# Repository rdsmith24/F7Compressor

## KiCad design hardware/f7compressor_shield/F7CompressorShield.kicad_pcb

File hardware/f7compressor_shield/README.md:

# F7Compressor carrier PCB (NUCLEO shield)

KiCad 10 project for a board that the NUCLEO-H723ZG plugs into directly,
replacing the point-to-point jumper wiring in `../../wiring_diagram.html`
between the NUCLEO and the LCD module, relay module, oil-pressure switch,
e-stop, and 4-20mA pressure loop. Open `F7CompressorShield.kicad_pro`.

## What's actually in this first pass

- **Schematic (`.kicad_sch`)**: complete and ERC-clean (0 errors, 0 warnings).
  Every net is named after the signal names used elsewhere in this repo
  (`FMC_D0`, `TP_SCK`, `RELAY_RUN`, `OIL_SW`, `ESTOP`, `PRESSURE_SENSE`,
  etc.) and was transcribed pin-by-pin from the FMC/SPI5/Analog&Digital I/O
  tables in `wiring_diagram.html`. Pins that are intentionally not used are
  marked with no-connect flags rather than left silently floating, so the
  schematic documents "unused" vs. "forgot to wire" explicitly.
- **PCB (`.kicad_pcb`)**: all 23 footprints (14 components + 4 LCD mounting
  holes + 5 Nucleo mounting holes) placed with correct net assignments, on
  **one unified board outline** (191.23 x 182.65mm). **Fully routed**: all
  39 nets, 2 layers, 537 track segments, 23 vias, 0 unconnected items —
  see "Routing" below for how.
- Two footprint groups on that one outline:
  - **NUCLEO-mating cluster** (`U1`, `CN7`-`CN10`), top-left: laid out to
    mirror where these connectors actually sit under the real NUCLEO-144
    board, with a **true-to-size reference outline** (70 x 133.34mm —
    the full board *with* the ST-Link section, since that's staying
    attached; `Dwgs.User` layer) drawn around it and 5 mounting holes
    (4 corners + 1 off-center, matching UM1974 Figure 7) — see "Mechanical
    layout" and "Nucleo mounting holes" below.
  - **Field-wiring group** (`J1`, `J2`, `SW1`-`SW3`, `J5`, `J6`, `R1`, `C1`, plus
    4 unreferenced LCD mounting-hole footprints): the LCD header (`J1`)
    top-right — positioned and surrounded by 4 mounting holes that
    reproduce the real LCD module's hole pattern, see "LCD mounting" below
    — with the relay header, simulation toggle switches, and pressure-loop
    terminal stacked below it, i.e. to the right of the Nucleo cluster and
    down from the LCD, per request. Each part is left-aligned and stacked
    using its own real footprint bounding box (`stack_right()` in
    `gen_pcb.py`), so the gaps stay correct no matter how large or
    asymmetric an individual footprint's silkscreen/pads are (the terminal
    block and the resistor, in particular, both extend well to one side of
    their placement origin).
- Reference designators: `CN7`–`CN10` are the NUCLEO Zio headers (female
  sockets, mate directly with the NUCLEO board), `U1` is the Morpho
  connector pair (CN11+CN12, see below), `J1` is the LCD module header,
  `J2` is the relay module's control header, `SW1`-`SW3` are the on-board
  MTS-1 toggle switches (oil switch / e-stop / motor run sense), `J5` is
  the pressure-loop field terminal, `J6` is the 5VDC power input terminal
  (see "Power input" below), `R1`/`C1` are the pressure loop's 150Ω shunt
  and 100nF decoupling cap.

## Oil switch / e-stop / run-sense: on-board MTS-1 switches, not field terminals

`OIL_SW` and `ESTOP` used to be 2-pin screw terminals for wiring in the
real field switches. They're now **on-board MTS-1 SPDT toggle switches**
(`SW1`, `SW2`) instead, so the oil-pressure-fault and e-stop conditions can
be flipped directly on the bench without needing the actual field hardware
wired up — useful for firmware bring-up. `SW3` adds a third switch for a
**`RUN_SENSE`** net simulating motor-running feedback (see below).

- Each switch is used as a simple SPST: the common pole (pin 2, physically
  the MTS-1's center pin) goes to the signal net (`OIL_SW` / `ESTOP` /
  `RUN_SENSE`), one throw (pin 1) goes to `GND`, and the third throw (pin 3)
  is left unconnected. Toggling the switch mimics a NC switch's two states —
  closed (pin2–pin1 connected, net pulled to GND) or open (net floating,
  pulled HIGH by the MCU's internal pull-up).
- **Real part: Dailywell `1MS1T1B1M1QES-5`** (SPDT, PC-pin, same MTS-1
  family). No bundled KiCad footprint matches it, so `gen_pcb.py`'s
  `make_mts1_footprint()` builds it directly: 3 round THT pads, center pad
  (pin 2, common) drawn square to mark pin 1. Pin spacing confirmed against
  the real part's own listed dimensions at **4.70mm** — matches this
  footprint exactly, no change needed.
- **No PCB mounting hole for the bushing**: the real part has a confirmed
  6.35mm (0.25") mounting bushing, but that's nearly as wide as its whole
  body (6.86mm) — there's no room for it to sit beside the 3 pins within
  that footprint. That's strong physical evidence this bushing mounts
  through an enclosure panel cutout, not the PCB (the electrical pins
  solder to the board; the switch's mechanical mounting is panel-side).
  Confirmed with the user before leaving it out rather than guessing a
  PCB-side hole position that doesn't physically make sense.
- `J3`/`J4` (the old terminal references) no longer exist; `J5` (pressure
  loop) is unchanged since it isn't a switch — the 4-20mA loop still needs
  a real field terminal, not a toggle.

### Generic 3D model for `SW1`-`SW3`

No bundled or downloadable 3D model matches this part (or any close
MTS-1-family equivalent), so a simple placeholder was built by hand —
`3dmodels/SW_MTS1_generic.wrl`, a black box (body) plus a cylinder+sphere
(lever stub), sized to the real part's known 12.7 x 6.86mm body envelope.
It's explicitly a generic stand-in for visualization ("can be any brand"),
not a dimensionally accurate model of the real switch.

Attaching it surfaced a real scaling bug, found by measurement rather than
guessing: KiCad interprets raw VRML coordinates at a fixed 2.54 scale
(mm per 0.1", a legacy VRML convention) regardless of what unit the model
was actually authored in. The model here is authored directly in mm, so
`m_Scale = 1/2.54` is needed to display it correctly. The first attempt
assumed the usual inches-to-mm factor (`1/25.4`) and undershot by 10x
(rendered as a barely-visible speck); the actual factor was found by
pixel-measuring the rendered box at `scale=1.0` against the footprint's
own known pad pitch (a precise, calibrated measurement, not an estimate)
and solving for the scale that makes the box match the real 12.7 x 6.86mm
footprint outline exactly — confirmed by rendering again afterward and
re-measuring. Model path is `${KIPRJMOD}/3dmodels/SW_MTS1_generic.wrl`,
project-relative so it travels with the repo.

### `RUN_SENSE` (`SW3`) — new signal, not in firmware yet

There is **no existing motor-running-feedback input anywhere in this
project** — `CLAUDE.md`'s state machine only ever commands the relay
(`RELAY_RUN`), it never reads back whether the motor actually started. This
switch wires up a net for that *future* feature, the same way the spare
relay channels (`RELAY_IN2`-`4`) were wired for future use:

| Net | MCU pin | NUCLEO connector | Configured anywhere today? |
|---|---|---|---|
| `RUN_SENSE` | `PC3` | CN9 pin 5 (Zio) | No — not in CubeMX, not in `CLAUDE.md`, not read by any firmware |

`PC3` was picked because, like `PD6`/`PB1` for the spare relay channels,
it's unclaimed by any peripheral in `CLAUDE.md`'s pin tables. Using it for
real motor-run sensing later would need: CubeMX GPIO-input config for
`PC3`, a firmware read of it (e.g. in `compressor_sm.c`'s `RUNNING` state
to detect a stall/failed-start condition), and deciding what the state
machine should actually *do* with that information — none of which this
PCB-only change touches.

## Relay header (J2) — all 4 channels wired

The relay module is a 4-channel board but the firmware only drives channel
1 (`RELAY_RUN` = `PG4`, CN12 pin 69). The other 3 channels are now wired on
this board too, for future use, even though nothing drives them yet:

| J2 pin | Net | MCU pin | NUCLEO connector | Driven by firmware today? |
|---|---|---|---|---|
| 3 (IN1) | `RELAY_RUN` | `PG4` | CN12 pin 69 (Morpho) | Yes — `relay.c` |
| 4 (IN2) | `RELAY_IN2` | `PG5` | CN12 pin 68 (Morpho) | No — CubeMX already configures it as a GPIO output (`CLAUDE.md`), just unused |
| 5 (IN3) | `RELAY_IN3` | `PD6` | CN9 pin 4 (Zio) | No — not configured by CubeMX at all yet |
| 6 (IN4) | `RELAY_IN4` | `PB1` | CN9 pin 7 (Zio) | No — not configured by CubeMX at all yet |

`PG5`/`PD6`/`PB1` were picked because they're genuinely unclaimed by any
other peripheral in `CLAUDE.md`'s pin tables. Before IN2–IN4 can actually
be used, `PD6` and `PB1` need to be configured as GPIO outputs in CubeMX
(`PG5` already is) and the firmware needs a `Relay_Request()`-style call
added for each channel — this board only adds the physical wiring, it
doesn't change firmware.

## Power input (J6)

`J6` is a 2-pin screw terminal for an external 5VDC supply, so one
connector on this board can power the Nucleo and everything downstream of
it. **Real part: Phoenix Contact `1727010`** (MKDS 1/2-3,81 — confirmed
2-position, 3.81mm pitch, horizontal THT from distributor listings). KiCad
ships this exact footprint
(`TerminalBlock_Phoenix_MKDS-1-2-3.81_1x02_P3.81mm_Horizontal`), used
directly — no custom part needed, unlike the switches above. This
replaced the earlier generic placeholder (`TerminalBlock_MaiXu_MX126`,
5.08mm pitch). `J5` (pressure loop) uses the same real part and footprint
now too, once a part number was given for it.

- `J6` pin 1 (`+5V_IN`) goes to `U1` pin 6 — **Morpho CN11 pin 6, E5V** —
  the documented primary power source for this whole project
  (`wiring_diagram.html`'s Power table: "External 5 VDC adapter | CN11
  pin 6 (E5V) | Primary power source"). `J6` pin 2 goes to `GND`.
- **This is deliberately a separate net from the existing `+5V`** used for
  the relay module's VCC (sourced from Zio `CN8` pin 9). `CN8` pin 9 is
  the *Nucleo's own* regulated pass-through output, derived from E5V
  through the Nucleo's on-board power-source mux/protection circuitry —
  tying `+5V_IN` directly to it on our board would bypass that circuitry
  instead of feeding it properly. Once E5V is powered, `CN8` pin 9 should
  carry the same rail anyway (via the Nucleo's own hardware), so the
  relay's `+5V` wiring doesn't need to change.
- **A jumper move on the physical Nucleo board is required for this to
  actually work**: `JP2` has to be set to the `EXT` position (pins 5-6),
  per `CLAUDE.md`'s hardware summary — this is a jumper on the Nucleo
  itself, not something this shield can set for you.
- A `PWR_FLAG` symbol is attached to `+5V_IN` in the schematic — not a
  real component, just a standard KiCad marker asserting "this net is
  externally driven," needed because `E5V` is a `Power input`-typed pin
  that ERC otherwise expects a driving `Power output` pin for.

## What's routed vs. just present

Only the nets actually used by this design are wired — everything else on
the Zio/Morpho headers is populated (for mechanical fit) but left on
no-connect. See `CLAUDE.md` for the full signal-to-pin reference this was
built from.

## Morpho: CN11 and CN12 are real, separate connectors (not a combined part)

Three FMC data lines (`PD8`/`PD9`/`PD10` = `FMC_D13`-`D15`) and the RUN
relay (`PG4`) are only reachable on the Morpho connectors (CN11/CN12),
which are unpopulated from the factory — you solder male pin headers onto
the Nucleo at those two locations, and this shield needs matching female
sockets.

**This went through two iterations.** The first used KiCad's bundled
`Module:ST_Morpho_Connector_144_STLink` footprint (via the official
`MCU_Module:NUCLEO144-F429ZI` symbol) as a single combined part for both
CN11 and CN12, with pad numbers cross-checked against `CLAUDE.md`'s known
signals (pad N = CN11 pin N for N 1-72, pad N = CN12 pin N-72 for N
73-144 — `PD9`→pad 69→CN11 pin 69, `PG4`→pad 141→CN12 pin 69, `PD8`→pad
82→CN12 pin 10, `PD10`→pad 137→CN12 pin 65, all four verified). That
worked electrically, but direct inspection (prompted by counting pins on
the real board) found two real problems with it:

- The real `CN11`/`CN12` are each **35×2 (70-pin)** headers, confirmed
  from the NUCLEO-H723ZG schematic (sheet 5, "MORPHO CONNECTOR LEFT/RIGHT
  SIDE", labeled "Header 35x2"). `CLAUDE.md` previously said 2×38, which
  was wrong and has been corrected. The bundled footprint has 74 pads per
  side (148 total) — 8 more than the real connectors.
- It's **one footprint representing two physically separate connectors**,
  which doesn't match the real board and isn't something you can order as
  a single part.

**Current design**: `CN11` and `CN12` are two separate instances of the
same plain `Connector_Generic:Conn_02x35_Odd_Even` / `PinSocket_2x35_
P2.54mm_Vertical` part already used (and pin-1-verified) for `CN7`-`CN10`
— exactly 70 pads each, nothing extra. Pin numbers and GPIO assignments
are ST's own real-board numbering, from UM1974 Table 21 ("ST morpho
connector for NUCLEO-F207ZG, ..., NUCLEO-H743ZI" — the same family this
H723ZG board belongs to) — cross-checked against `CLAUDE.md` and found to
match exactly for all six signals actually used (`FMC_D13`→CN12 pin 10,
`FMC_D14`→CN11 pin 69, `FMC_D15`→CN12 pin 65, `RELAY_RUN`→CN12 pin 69,
`RELAY_IN2`→CN12 pin 68, `+5V_IN`→CN11 pin 6).

**Pin-1 orientation for CN11/CN12**, determined the same rigorous way as
`CN7`-`CN10`/`J1` (see below) rather than assumed: zoomed into UM1974's
whole-board mechanical drawing (Figure 6) at both connectors' own pads and
found the square pin-1 marker on the **left column** for both — same
absolute direction for both connectors, not mirrored between them, even
though CN11 and CN12 sit on opposite sides of the board. Placed using the
same `place_mirrored()` helper as the Zio headers.

This closes Open Item 1 from the original plan — the Morpho pad mapping
is no longer a guess, and the connectors now mechanically match the real
board part-for-part.

## Mechanical layout (grounded in ST's own drawing, not arbitrary anymore)

The first draft of this board spread `CN7`-`CN10` and `U1` arbitrarily far
apart purely to dodge DRC overlap — that didn't look or behave like a real
shield, and isn't what a shield should look like. This pass fixes that
using ST's own **UM1974 "Nucleo-144 board mechanical drawing in
millimeter"** (Figure 6), fetched from st.com, plus the bundled
`ST_Morpho_Connector_144_STLink` footprint's own verified pad geometry:

- The footprint's own CN11 pads sit at local x = 0-2.54mm and CN12 pads at
  x = 60.96-63.5mm — a 63.5mm outer span that matches UM1974's dimensioned
  "63.50mm" cuttable-target-board width exactly, confirming the footprint's
  internal coordinate frame is physically accurate and can be used directly
  as the board-cluster frame, with `U1`'s own placement origin landing
  exactly on CN11 pin 1.
- `CN7`/`CN8`'s pin-1 offsets *from that same origin* were pixel-measured
  directly off the drawing (centroid-detecting each header's square pin-1
  pad in a 600dpi render of UM1974 Figure 6, calibrated against the
  header's own known 2.54mm pin pitch measured the same way):
  `CN8` ≈ (7.48, 9.78) mm from CN11 pin 1, `CN7` ≈ (53.66, 0.22) mm from
  CN12's first pad. `CN9`/`CN10` are stacked directly below `CN8`/`CN7`
  using each header's own real pin-row span (17.78mm / 22.86mm) plus a
  2.54mm gap — they physically stack in one column on the real board too.
- This replaced an earlier version that *guessed* the Zio inboard offset
  (~5-10mm, not measured) — that guess turned out to collide with `U1`'s
  real pads once real mounting holes were added (see "Nucleo mounting
  holes" below), which is what prompted re-measuring `CN7`/`CN8` properly
  instead of patching around the collision.

**What's still approximate**: this is a hand pixel-measurement of a scanned
legacy drawing (UM1974 shows the original MB1137 board, not this project's
exact MB1364/H723ZG revision — ST keeps Zio/Morpho positions identical
across the whole Nucleo-144 family specifically so shields stay compatible
across revisions, which is why this is still a reasonable basis), with
roughly 1-2mm / 2-3% of calibration uncertainty based on cross-checking
the measured `CN12` pad position against its known-exact footprint
location. Good enough to avoid real collisions (confirmed below), not a
substitute for checking against UM2407 (the H7-specific manual) or the
physical board before fab.

**Expected DRC findings from this intentional overlap**: because the
NUCLEO-mating cluster deliberately places `CN7`-`CN10` inside `U1`'s
courtyard (that's the whole point — the Zio pins really do sit in the same
board area the Morpho pins occupy on a real stacked shield), DRC reports
courtyard-overlap / PTH-inside-courtyard violations between `U1` and each
of `CN7`-`CN10`, plus a couple of silkscreen-clearance warnings from the
tight stacking. These are expected for this design pattern, not placement
mistakes — any real NUCLEO-144 shield hits the same checks. They'd
normally be added as DRC rule exclusions once the layout is final rather
than "fixed" by spacing things out again.

**True-size reference outline**: an earlier pass drew only a tight
bounding box around `U1`/`CN7`-`CN10` as the "Nucleo footprint," which
looked (and was) noticeably smaller than a real Nucleo-144 board. There's
now a proper **70 x 133.34mm reference rectangle** (`Dwgs.User` layer, not
`Edge.Cuts` — same treatment as the LCD outline below) at the board's real
size. It's anchored so its top-left corner sits at the standard board
margin; the 6.5mm of width beyond the Morpho footprint's own 63.5mm span
is a confirmed number from UM1974's dimension chain, split evenly
left/right as a documented assumption (the drawing doesn't say how it
splits); the 44.44mm of height beyond the Morpho pad span is centered
top/bottom the same way. Treat this outline as a size/scale reference, not
a precise registration aid.

## Nucleo mounting holes

5 `MountingHole_3.2mm_M3` footprints (no net), for standoffs supporting
the Nucleo board (ST-Link section included — see above).

UM1974 Figure 6 (mm) / Figure 7 (mil, same drawing) shows **5** filled-dot
markers — 2 at the ST-Link/target cut line (near `CN8`/`CN7`), 2 further
down (near `CN9`/`CN10`), and a 5th ~2/3 of the way down the board, offset
right of center (near the ADC_IN/QSPI boundary on the right-hand header),
not at the middle of the other 4. Each dot's pixel position was
centroid-detected in the same 600dpi render used for `CN7`/`CN8` above,
and converted to mm **relative to CN11 pin 1** (`U1`'s own placement
origin) using the same local pin-pitch calibration — i.e. the holes and
the headers are measured in one consistent frame now, not two separate
ones:

| Hole | Position (mm from `U1`'s origin) | Near |
|---|---|---|
| top-left | (7.91, -3.39) | `CN8`/`CN11` top |
| top-right | (56.96, -3.00) | `CN7`/`CN12` top |
| middle | (41.48, 49.26) | right header, ADC_IN/QSPI boundary |
| bottom-left | (9.39, 73.70) | `CN8`/`CN9` boundary |
| bottom-right | (55.96, 73.57) | `CN7`/`CN10` boundary |

**This superseded an earlier, dropped attempt**: the first try measured
the 5 holes as a rectangle relative to *each other*, independent of the
connectors, and when placed absolutely it landed directly on `U1`'s real
Morpho pads — a genuine `hole_clearance` DRC error (an actual "can't
drill there" collision), not the already-expected courtyard-overlap kind.
Rather than paper over that by moving the holes to the board's corners
(which stopped being faithful to the drawing), `CN7`/`CN8` got re-measured
properly instead (see "Mechanical layout" above) so holes and headers
share one coordinate frame. With that fix, all 5 holes sit close to the
header boundaries — the same place they are on the real drawing — with no
real DRC collisions (confirmed: no `hole_clearance`, `solder_mask_bridge`,
or `hole_to_hole` violations; only the already-documented courtyard/NPTH
findings from sitting near `U1`'s courtyard).

Same calibration-uncertainty caveat as above applies — verify against the
physical board or UM2407 before drilling.

## LCD mounting (grounded in the module's own 2D drawing)

`Documentation/3.2inch_320x240_Touch_LCD_2D.pdf` ("HY32E-size.dwg") is a
fully-dimensioned mechanical drawing of the Waveshare 3.2" LCD module, so
the LCD's mounting holes and connector position are reproduced from it
rather than guessed:

- **4 mounting holes** (`MountingHole_3.2mm_M3`, no net — pure mechanical
  footprints) reproduce the LCD board's own hole pattern exactly: 79.00mm
  apart in X, 54.00mm apart in Y. Both spacings are explicit dimensions on
  the drawing (`79.00±0.1` and `54.00`), and `4.00 + 54.00 + 4.00 = 62.00`
  ties out exactly against the drawing's overall board height — strong
  confirmation these four numbers are the right ones to trust (the sheet
  has other dimensions that don't tie out as cleanly, and were not used).
  Mount the LCD on M3 standoffs through these holes.
- **`J1`** is positioned from the same anchor (the top-left hole): the
  drawing dimensions the connector's top pin as 6.67mm below the top-left
  hole, visually in line with it in X. So once the LCD is standoff-mounted
  at the 4 holes, its real P1/P2 connector should land directly on `J1` —
  that's the point of grounding both the holes and the connector in the
  same drawing instead of eyeballing them independently.
- A **reference outline** of the full LCD footprint (94.97 x 62.00mm) is
  drawn on the `Dwgs.User` layer (not `Edge.Cuts` — it's not part of this
  board's own cut shape, just a visual "the LCD sits here" reference,
  visible in the KiCad PCB editor but not in the quick renders above).
- **Confidence**: the hole pattern and overall outline are solid (multiple
  dimensions tie out exactly, see `gen_pcb.py`'s comments). The
  connector's X alignment to the hole column is a visual read of the
  drawing, not off an explicit dimension — worth confirming against the
  physical LCD board before final assembly. The drawing also confirms the
  LCD module exposes **male** pins (matching the female-socket assumption
  for `J1` below), which resolves half of Open Item 1.

## `J1` pin 1/3 were swapped — a real hardware-safety bug, now fixed

Checking `J1` against the LCD's own manufacturer schematic
(`Documentation/3.2inch-320-240-Touch-LCD-SCH-2.pdf`, read pin-by-pin via
exact PDF text coordinates rather than eyeballed) found that real `P1`/`P2`
pin 1 is **`DC-5V`** (a required power input), not `FMC_D0` — the data
bus actually starts at pin 3, with pins 1/2 being power/ground:

| Pin | Real signal (LCD schematic) | What this project had |
|---|---|---|
| 1 | `DC-5V` (5V power in) | `FMC_D0` |
| 2 | `GND` | `GND` ✓ |
| 3 | `D0` | `GND` |
| 4-34 | `D1`...`D15`, `LCD_CS`, `RS`, `WR`, `RD`, `RST`, `BL_CTRL`, `TP_*`, `VCC-3V3`, `GND` | all already matched ✓ |

Every other pin (4 through 34) already matched the real schematic exactly
once cross-checked — this was an off-by-one-pair error isolated to just
the first two positions, not a wholesale mismatch. It also existed in the
project's own `wiring_diagram.html` (said pin1=`D0`, pins2-3=`GND`), which
has been corrected too, including adding the previously-undocumented real
pin 1 (`DC-5V`/`+5V`, required power, not previously wired at all).

**Caught before it mattered**: confirmed with the user that nothing is
physically jumper-wired to the LCD yet, so this never reached real
hardware. Fixed by changing `J1`'s net assignment only (pin 1 → `+5V`,
pin 3 → `FMC_D0`); nothing else changed, since everything else was
already correct. Re-verified ERC clean and the new pad positions
numerically (pin 1 and pin 3 land on the same physical column, as
expected for two odd-numbered pins on a 2-row header). Board was fully
re-routed.

## Pin-1 orientation fix (`CN7`-`CN10`, `CN11`, `CN12`, `J1`)

Caught by inspection against the mechanical drawings, not something the
earlier pin-mapping work checked: the generic KiCad "Odd_Even" connector
footprint's pad 1/2 column assignment doesn't match the real silkscreen on
either the Nucleo or the LCD module. Verified directly rather than just
asserted:

- **Nucleo Zio headers**: on our board, `U1` (Morpho/CN11) sits at
  X=8.25mm; `CN8` pad "1" was at X=15.73mm and pad "2" at X=13.19mm — pad
  2 is the column physically closer to the Morpho connector. But UM1974's
  drawing (zoomed on the real `CN8`/`CN11` silkscreen) shows pin 1 (the
  "NC" square pad) is the column **closer** to CN11. Same check on `CN7`
  against `CN12` confirmed the identical mismatch. So pads 1↔2 (and every
  odd/even pair: 3↔4, 5↔6, ...) were physically swapped on all four Zio
  headers (`CN7`-`CN10` all share the same footprint convention).
- **LCD header**: `J1` pad 1 landed on the *inner* column (toward the
  display) once placed at the measured LCD-hole-aligned origin, but the
  LCD's own 2D mechanical drawing
  (`Documentation/3.2inch_320x240_Touch_LCD_2D.pdf`) shows pin 1 on the
  *outer* column (toward the board edge) of its left-side header. Same
  mismatch, same fix.
- **Fix (final form)**: the footprints themselves are mirrored left-right
  in `gen_pcb.py` (`place_mirrored()`), not the net assignment — net
  numbering in `gen_sch.py` is the natural, un-swapped
  `pin_mapping.md`/`wiring_diagram.html` numbering. An earlier version of
  this fix swapped net assignments pairwise instead of touching the
  footprint, which is electrically equivalent but leaves the square
  "pin 1" silkscreen marker (geometry that belongs to the pad itself, not
  a label) sitting at the *wrong* physical location — still visually
  wrong when compared against the real board, which is what caught it.
  `FOOTPRINT.Mirror()` isn't usable from Python scripting (hits an
  unimplemented base-class virtual — `"Mirror used, should not occur"`),
  so `place_mirrored()` mirrors every pad and graphical item's local X
  coordinate by hand, about the *midpoint* between the two pad columns
  (mirroring about pad 1's own position was tried first and is wrong — it
  leaves pad 1 fixed and only moves everything else, not a real column
  swap; caught by checking the resulting pad positions numerically before
  trusting it). Re-verified against real pad positions after the fix:
  pad 1 is now the column closer to Morpho on all four Zio headers, and
  `J1` pad 1 (`FMC_D0`, the LCD's real physical pin 1) is now on the
  outer column, matching both mechanical drawings. ERC/DRC clean; the
  board was fully re-routed since net-to-pad geometry changed.
- **CN11/CN12**, added after the Morpho split above, use the exact same
  `place_mirrored()` fix as `CN7`-`CN10` — they're the same footprint
  family, so the same risk applies. Pin 1's real location (left column,
  confirmed from UM1974 Figure 6) was determined *before* placing them,
  not discovered as a bug afterward this time.
- **Not checked for this**: `J2`, `J5`, `J6`, `SW1`-`SW3` don't have this
  risk, since both ends of those connections are defined by this project,
  not an external fixed pinout to mismatch against.

**Second bug found and fixed while adding CN11/CN12**: `place_mirrored()`
mirrors pad/graphic positions by hand (see above), but was then calling
`fp.SetPosition(pos_mm)` directly — which moves the footprint's *anchor*
to `pos_mm`, not pad 1. Because the hand-mirror doesn't move the anchor
itself, pad 1 ends up one full pin pitch (2.54mm) away from `pos_mm`, not
at it. Caught by comparing `CN8`'s actual pad-1 position against
`CN8_OFFSET`'s intended target: they differed by exactly 2.54mm. This
affected every connector `place_mirrored()` had touched — `CN7`-`CN10`
and `J1` were each mechanically offset by one pin pitch from their
intended, pixel-measured positions (still on the *correct side*, since
mirroring direction was unaffected, just not at the *correct distance*).
Fixed by computing pad 1's post-mirror local offset from the anchor and
solving for the anchor position that puts pad 1 exactly at `pos_mm`.
Re-verified numerically after the fix: all six mirrored connectors'
(`CN7`, `CN8`, `CN9`, `CN10`, `CN11`, `CN12`) pad 1 now lands exactly on
its intended target coordinate, not offset.

## Routing

All 39 nets are routed (2 layers, 537 track segments, 23 vias, 0
unconnected items) using **Freerouting** (the standard open-source
autorouter the KiCad community uses for this — `kicad-cli` has no
autorouter of its own):

- `gen_pcb.py`'s board was exported to Specctra DSN (`pcbnew.ExportSpecctraDSN`)
  and routed with `freerouting-cli`/`freerouting.jar` v2.5.0, run by hand
  outside this repo (`-de F7CompressorShield.dsn -do F7CompressorShield.ses`).
  The native `freerouting-cli` binary hit a GraalVM native-image bug
  (`SerializationConstructorAccessor class not found`) partway through
  routing on this machine; the plain `.jar` run with a regular JVM worked.
- `pcbnew.ImportSpecctraSES()` (the normal way to bring a routed `.ses`
  back into KiCad) silently returned `False` here with no further error —
  possibly a limitation of this scripted/headless path rather than the
  interactive GUI import. Worked around it with a small custom importer
  (`routing/apply_ses.py`, not part of the KiCad project itself) that
  parses the `.ses` file's own S-expression routing data directly and
  creates the matching `PCB_TRACK`/`PCB_VIA` objects via the pcbnew
  Python API — net names, coordinates, and the via padstack size were all
  cross-checked against the DSN export before trusting the conversion.
- Freerouting's default track width (0.15mm) was below this board's
  declared minimum (0.2mm, netclass `Default`) and got flagged by DRC;
  every track narrower than 0.2mm was widened to exactly 0.2mm as part of
  the import step, which didn't introduce any new clearance violations.
- The route produced after the pin-1 mirror fix (above) left 3 genuine
  `clearance` violations (0.12-0.20mm actual vs. 0.2mm required) in two
  tight spots: a `BL_CTRL` via sitting too close to a diagonal `FMC_NE1`
  trace, and a short `BL_CTRL` dodge-around-`CN7`-pad-11 jog. Fixed by
  directly repositioning the via and the two dodge points with pcbnew
  scripting (not a full re-route) — computed from the actual track/pad
  geometry on the board, not guessed. The first via move (perpendicular
  to just the `FMC_NE1` trace) over-corrected into a *new* violation
  against an unrelated nearby `FMC_D15` trace, caught by re-running DRC
  immediately rather than trusting the hand calculation; the final
  position was solved for clearance against both tracks simultaneously.
  Re-verified clean (0 `clearance` findings, 0 unconnected) after.
- The re-route after the CN11/CN12 split (above) left 4 more `clearance`
  violations: a long `RELAY_IN3` trace (CN9 pin 4 to J2 pin 5) squeezed
  too close to both `CN10` pad 19 and a `J2` GND pad in the same tight
  spot (the two constraints left essentially zero margin for a single
  straight segment — a perpendicular nudge that cleared one made the
  other worse), and a short `GND` trace too close to a `CN8` pad. Fixed
  by computationally searching for a clear detour path, checking every
  candidate against *all* nearby pads **and tracks** (not just pads — an
  earlier instinct to check pads only is exactly why the first nudge
  attempt above over-corrected) before committing to it, then replacing
  only the exact flagged segments by precise coordinate match. First
  attempt at the `RELAY_IN3` detour used a bounding-box removal that
  over-matched an unrelated upstream segment and anchored the new path to
  the wrong endpoint (off by 0.14mm from the real one) — introduced
  dangling tracks, a crossing, and 2 unconnected items; caught by
  re-running DRC immediately rather than assuming the detour worked, and
  redone with exact segment identification instead. Re-verified clean (0
  `clearance`, 0 unconnected, no dangling/crossing) after.
- The re-route after the `J1` pin 1/3 fix (above) left one more
  `clearance` violation: a `BL_CTRL` via sitting in a spot packed with
  `CN12` pads and five other FMC nets (`FMC_D4`-`D7`, `D11`) on both
  copper layers. An exhaustive grid search (±0.8mm, every 0.01mm) found
  **no position** for a standard 0.6mm via that cleared every nearby pad
  and track simultaneously. A single- and two-bend reroute entirely off
  this via (a plain two-segment F.Cu detour) looked clean at first, but
  the clearance checker used to verify it only checked endpoint-to-segment
  distance, which misses two segments that cross cleanly in their
  interior — DRC caught the resulting `tracks_crossing` against an
  unrelated `LCD_RST` trace immediately after. Reverted that detour,
  fixed the checker to test for true intersection, and instead just
  shrank both vias at this spot to 0.5mm (this board's declared minimum,
  `min_via_diameter` in the project file) at their **original, unmoved**
  positions — confirmed clear with 0.23mm/0.25mm margin, no geometry
  change needed at all once the via was the right size for how tight the
  neighborhood actually is.
- The re-route after swapping in the real `SW1`-`SW3`/`J6` part footprints
  (above) shifted the board layout slightly and left 4 more `clearance`
  violations, all in different spots (`FMC_NE1` and `RELAY_IN4` each
  squeezed between two pad rows with no single straight line clearing
  both; `FMC_A0` similarly, needing a 2-bend detour found by a systematic
  bend-point search rather than guessing; and a `BL_CTRL` run pinched
  between an `FMC_NOE` via and the just-added `FMC_A0` detour, fixed with
  a deliberately small -0.03mm shift applied consistently across the
  whole connected straight run, not just the one flagged segment, so nothing
  was left dangling). Each fix was found by a general-purpose clearance
  checker that tests candidate paths/shifts against every nearby pad and
  track (not hand-picked guesses) before applying anything. Re-verified
  clean (0 `clearance`, 0 unconnected) after.
- DRC after routing: down to 26 findings (fewer than before routing, since splitting the combined Morpho footprint into two correctly-sized CN11/CN12 connectors removed most of the old courtyard overlap with the Zio headers), all in the
  already-documented expected categories (courtyard overlap from the
  intentional Zio/Morpho/mounting-hole proximity, a couple of silkscreen
  warnings from tight stacking) — nothing routing-related, and
  `0 unconnected items`.

**FMC bus signal integrity — checked, neither controlled impedance nor
length matching is needed**: measured routed lengths range 31-149mm
(`FMC_D13` to `FMC_D14`). FMC pins are `GPIO_SPEED_FREQ_VERY_HIGH`
(`Core/Src/fmc.c`), whose datasheet worst-case rise/fall time is 3.3ns
(Table 54, speed `11`, 50pF load — realistically more like 30pF/2.4ns for
the actual trace+pad+ILI9341-input capacitance here). Against the FMC's
own 62.5ns data-setup window (15 AHB3 cycles @ 240MHz):
- Worst-case unterminated-trace ringing settles in ~5-7ns (a few round
  trips on the longest, ~150mm traces) — **~9x margin** before the bus is
  latched.
- Worst-case length-mismatch skew (~130mm, longest vs. shortest) is
  ~0.8ns — **~80x margin**.

Some of the longer nets (`FMC_A0`, `FMC_D2`/`D3`/`D14`, `FMC_NE1`/`NOE`/`NWE`)
exceed the standard "1/6 rule" critical-length threshold for a 3.3ns edge
(~92mm), so reflections are plausible on those specific traces, but with
that much timing margin they're not a functional concern — this is
standard, common practice for 8080-style parallel LCD interfaces at this
speed. If extra ringing/EMI margin mattered, the usual cheap fix is
22-33Ω series resistors at the MCU end of the longer lines; not pursued
here since it isn't required.

**Not done**: no manual cleanup pass on Freerouting's routing choices (via
placement, trace geometry) — it's exactly what the autorouter produced,
unreviewed.

## Open items (still unresolved — check before this goes near a fab house)

1. **Relay connector gender & pitch**: assumed 2.54mm male header for the
   relay module's J1 (module exposes a female header). Not verified
   against the actual board. (The LCD connector's gender is now confirmed
   male by its mechanical drawing — see "LCD mounting" above — so only the
   relay module side of this item remains open.)
2. **Mechanical layout precision**: see above — grounded in ST's real
   drawing now, but the inboard offsets between the Nucleo cluster's own
   connectors are an approximation, not a digitized measurement. Verify
   against UM2407 or the physical board before fab. (The LCD's mounting
   holes and connector position, by contrast, come from explicit
   dimensions that tie out exactly — see "LCD mounting" above.)
3. **Routing wasn't reviewed.** See "Routing" above — it's un-cleaned-up
   autorouter output, not hand-checked for sensible via placement or trace
   geometry around the FMC bus specifically.
4. No fabrication-readiness pass (DFM, silkscreen legend, copper pour, DRC
   rule exclusions for the expected overlaps above, etc.) has been done.
   This is a first-pass electrical + mechanical design
   check, not a send-to-fab file.

## Verification performed

```
kicad-cli sch erc  F7CompressorShield.kicad_sch   # 0 errors, 0 warnings
kicad-cli pcb drc  F7CompressorShield.kicad_pcb   # 0 unconnected, 26 findings, all in the
                                                   # expected courtyard/silk categories from the
                                                   # intentional Zio/Morpho overlap (see above)
```

Every net was also manually cross-checked pin-by-pin against the FMC, SPI5,
and Analog & Digital I/O tables in `../../wiring_diagram.html`.

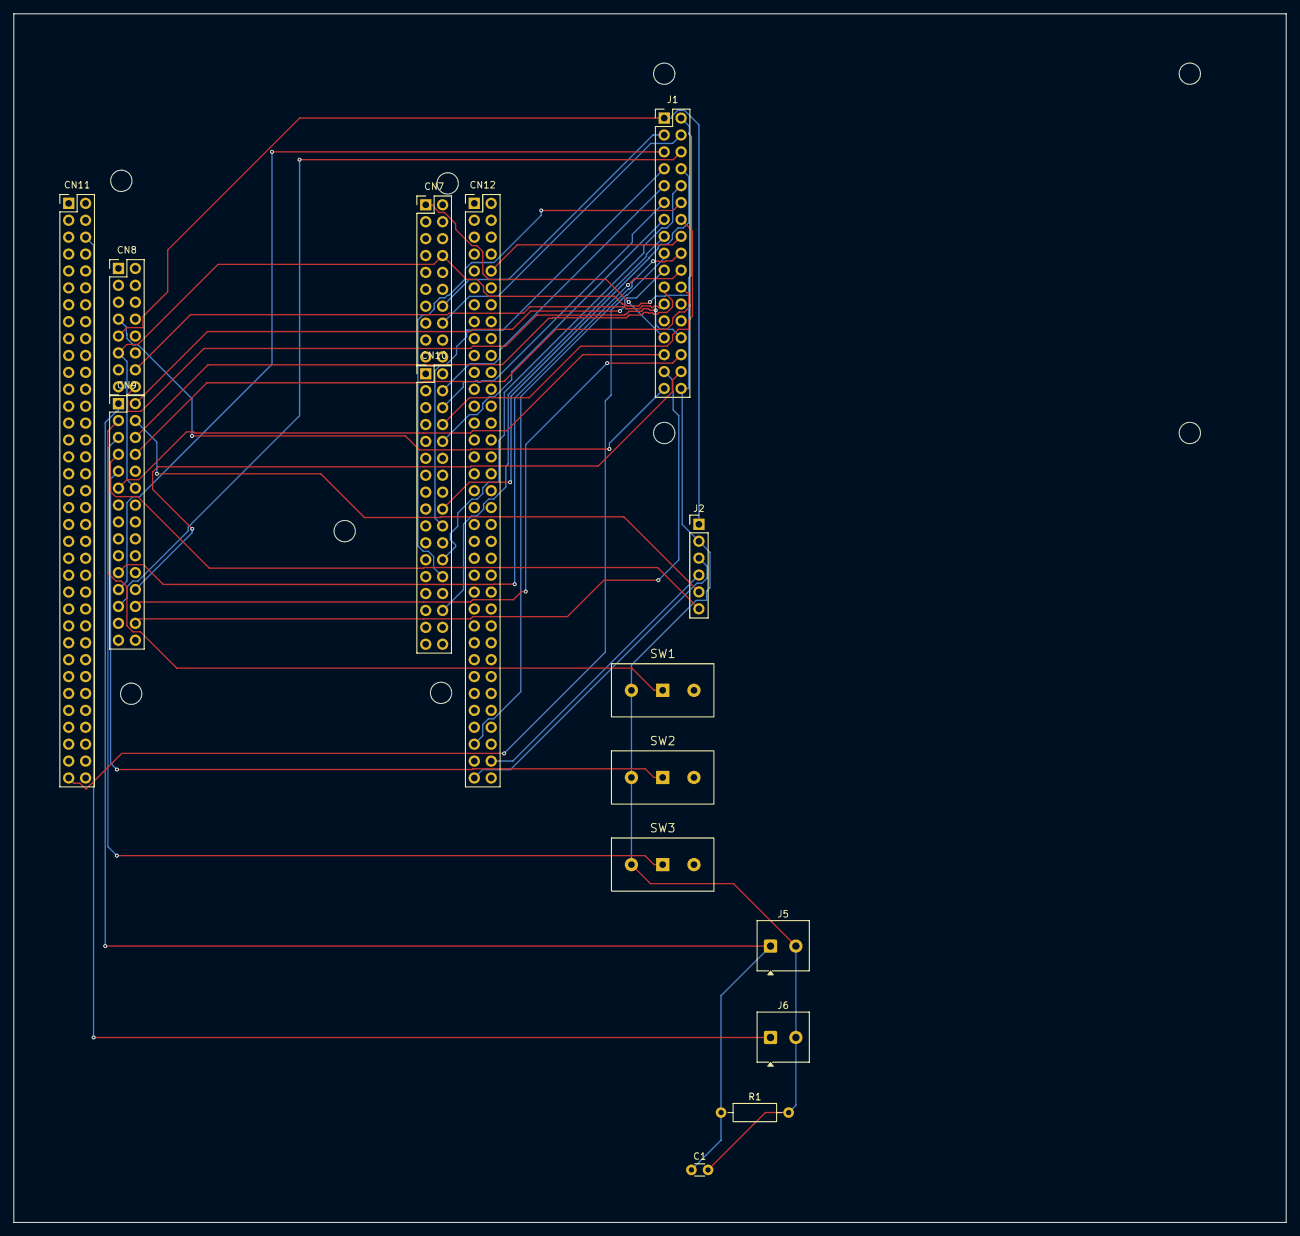
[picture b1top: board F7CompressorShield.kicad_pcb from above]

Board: 2 copper layers, 191.2 x 181.7 mm, 15 parts (0 on the bottom side), 39 nets.

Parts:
C1: C_Disc_D3.0mm_W1.6mm_P2.50mm
CN7: PinSocket_2x10_P2.54mm_Vertical
CN8: PinSocket_2x08_P2.54mm_Vertical
CN9: PinSocket_2x15_P2.54mm_Vertical
CN10: PinSocket_2x17_P2.54mm_Vertical
CN11, CN12: PinSocket_2x35_P2.54mm_Vertical
J1: PinSocket_2x17_P2.54mm_Vertical
J2: PinHeader_1x06_P2.54mm_Vertical
J5, J6: TerminalBlock_Phoenix_MKDS-1-2-3.81_1x02_P3.81mm_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; TerminalBlock_Phoenix_MKDS-1-2-3.81_1x02_P3.81mm_Horizontal
R1: R_Axial_DIN0207_L6.3mm_D2.5mm_P10.16mm_Horizontal
SW1, SW2, SW3: (no value)

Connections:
+3V3: CN8.7, J1.33
+5V: CN8.9, J1.1, J2.1
+5V_IN: CN11.6, J6.1
BL_CTRL: CN7.1, J1.27
ESTOP: CN9.9, SW2.2
FMC_A0: CN9.21, J1.20
FMC_D0: CN7.14, J1.3
FMC_D1: CN7.16, J1.4
FMC_D2: CN9.23, J1.5
FMC_D3: CN9.25, J1.6
FMC_D4: CN10.20, J1.7
FMC_D5: CN10.18, J1.8
FMC_D6: CN10.4, J1.9
FMC_D7: CN10.24, J1.10
FMC_D8: CN10.6, J1.11
FMC_D9: CN10.26, J1.12
FMC_D10: CN10.10, J1.13
FMC_D11: CN10.8, J1.14
FMC_D12: CN10.30, J1.15
FMC_D13: CN12.10, J1.16
FMC_D14: CN11.69, J1.17
FMC_D15: CN12.65, J1.18
FMC_NE1: CN9.2, J1.19
FMC_NOE: CN9.8, J1.22
FMC_NWE: CN9.6, J1.21
GND: C1.2, CN7.8, CN8.11, CN9.12, J1.2, J1.34, J2.2, J5.2, J6.2, R1.2, SW1.1, SW2.1, SW3.1
LCD_RST: CN8.14, J1.23
OIL_SW: CN9.3, SW1.2
PRESSURE_SENSE: C1.1, CN9.1, J5.1, R1.1
RELAY_IN2: CN12.68, J2.4
RELAY_IN3: CN9.4, J2.5
RELAY_IN4: CN9.7, J2.6
RELAY_RUN: CN12.69, J2.3
RUN_SENSE: CN9.5, SW3.2
TP_CS: CN9.11, J1.29
TP_IRQ: CN8.16, J1.28
TP_SCK: CN9.26, J1.30
TP_SDI: CN9.28, J1.31
TP_SDO: CN9.24, J1.32

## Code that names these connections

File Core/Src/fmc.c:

/* USER CODE BEGIN Header */
/**
  ******************************************************************************
  * File Name          : FMC.c
  * Description        : This file provides code for the configuration
  *                      of the FMC peripheral.
  ******************************************************************************
  * @attention
  *
  * Copyright (c) 2026 STMicroelectronics.
  * All rights reserved.
  *
  * This software is licensed under terms that can be found in the LICENSE file
  * in the root directory of this software component.
  * If no LICENSE file comes with this software, it is provided AS-IS.
  *
  ******************************************************************************
  */
/* USER CODE END Header */

/* Includes ------------------------------------------------------------------*/
#include "fmc.h"

/* USER CODE BEGIN 0 */

/* USER CODE END 0 */

SRAM_HandleTypeDef hsram1;

/* FMC initialization function */
void MX_FMC_Init(void)
{
  /* USER CODE BEGIN FMC_Init 0 */

  /* USER CODE END FMC_Init 0 */

  FMC_NORSRAM_TimingTypeDef Timing = {0};

  /* USER CODE BEGIN FMC_Init 1 */

  /* USER CODE END FMC_Init 1 */

  /** Perform the SRAM1 memory initialization sequence
  */
  hsram1.Instance = FMC_NORSRAM_DEVICE;
  hsram1.Extended = FMC_NORSRAM_EXTENDED_DEVICE;
  /* hsram1.Init */
  hsram1.Init.NSBank = FMC_NORSRAM_BANK1;
  hsram1.Init.DataAddressMux = FMC_DATA_ADDRESS_MUX_DISABLE;
  hsram1.Init.MemoryType = FMC_MEMORY_TYPE_SRAM;
  hsram1.Init.MemoryDataWidth = FMC_NORSRAM_MEM_BUS_WIDTH_16;
  hsram1.Init.BurstAccessMode = FMC_BURST_ACCESS_MODE_DISABLE;
  hsram1.Init.WaitSignalPolarity = FMC_WAIT_SIGNAL_POLARITY_LOW;
  hsram1.Init.WaitSignalActive = FMC_WAIT_TIMING_BEFORE_WS;
  hsram1.Init.WriteOperation = FMC_WRITE_OPERATION_ENABLE;
  hsram1.Init.WaitSignal = FMC_WAIT_SIGNAL_DISABLE;
  hsram1.Init.ExtendedMode = FMC_EXTENDED_MODE_DISABLE;
  hsram1.Init.AsynchronousWait = FMC_ASYNCHRONOUS_WAIT_DISABLE;
  hsram1.Init.WriteBurst = FMC_WRITE_BURST_DISABLE;
  hsram1.Init.ContinuousClock = FMC_CONTINUOUS_CLOCK_SYNC_ONLY;
  hsram1.Init.WriteFifo = FMC_WRITE_FIFO_ENABLE;
  hsram1.Init.PageSize = FMC_PAGE_SIZE_NONE;
  /* Timing */
  Timing.AddressSetupTime = 1;
  Timing.AddressHoldTime = 15;
  Timing.DataSetupTime = 15;
  Timing.BusTurnAroundDuration = 0;
  Timing.CLKDivision = 16;
  Timing.DataLatency = 17;
  Timing.AccessMode = FMC_ACCESS_MODE_A;
  /* ExtTiming */

  if (HAL_SRAM_Init(&hsram1, &Timing, NULL) != HAL_OK)
  {
    Error_Handler( );
  }

  /* USER CODE BEGIN FMC_Init 2 */

  /* USER CODE END FMC_Init 2 */
}

static uint32_t FMC_Initialized = 0;

static void HAL_FMC_MspInit(void){
  /* USER CODE BEGIN FMC_MspInit 0 */

  /* USER CODE END FMC_MspInit 0 */
  GPIO_InitTypeDef GPIO_InitStruct = {0};
  if (FMC_Initialized) {
    return;
  }
  FMC_Initialized = 1;

    LL_RCC_SetFMCClockSource(LL_RCC_FMC_CLKSOURCE_HCLK);

  /* Peripheral clock enable */
  __HAL_RCC_FMC_CLK_ENABLE();

  /** FMC GPIO Configuration
  PF0   ------> FMC_A0
  PE7   ------> FMC_D4
  PE8   ------> FMC_D5
  PE9   ------> FMC_D6
  PE10   ------> FMC_D7
  PE11   ------> FMC_D8
  PE12   ------> FMC_D9
  PE13   ------> FMC_D10
  PE14   ------> FMC_D11
  PE15   ------> FMC_D12
  PD8   ------> FMC_D13
  PD9   ------> FMC_D14
  PD10   ------> FMC_D15
  PD13   ------> FMC_A18
  PD14   ------> FMC_D0
  PD15   ------> FMC_D1
  PD0   ------> FMC_D2
  PD1   ------> FMC_D3
  PD4   ------> FMC_NOE
  PD5   ------> FMC_NWE
  PD7   ------> FMC_NE1
  */
  /* GPIO_InitStruct */
  GPIO_InitStruct.Pin = GPIO_PIN_0;
  GPIO_InitStruct.Mode = GPIO_MODE_AF_PP;
  GPIO_InitStruct.Pull = GPIO_NOPULL;
  GPIO_InitStruct.Speed = GPIO_SPEED_FREQ_VERY_HIGH;
  GPIO_InitStruct.Alternate = GPIO_AF12_FMC;

  HAL_GPIO_Init(GPIOF, &GPIO_InitStruct);

  /* GPIO_InitStruct */
  GPIO_InitStruct.Pin = GPIO_PIN_7|GPIO_PIN_8|GPIO_PIN_9|GPIO_PIN_10
                          |GPIO_PIN_11|GPIO_PIN_12|GPIO_PIN_13|GPIO_PIN_14
                          |GPIO_PIN_15;
  GPIO_InitStruct.Mode = GPIO_MODE_AF_PP;
  GPIO_InitStruct.Pull = GPIO_NOPULL;
  GPIO_InitStruct.Speed = GPIO_SPEED_FREQ_VERY_HIGH;
  GPIO_InitStruct.Alternate = GPIO_AF12_FMC;

  HAL_GPIO_Init(GPIOE, &GPIO_InitStruct);

  /* GPIO_InitStruct */
  GPIO_InitStruct.Pin = GPIO_PIN_8|GPIO_PIN_9|GPIO_PIN_10|GPIO_PIN_13
                          |GPIO_PIN_14|GPIO_PIN_15|GPIO_PIN_0|GPIO_PIN_1
                          |GPIO_PIN_4|GPIO_PIN_5|GPIO_PIN_7;
  GPIO_InitStruct.Mode = GPIO_MODE_AF_PP;
  GPIO_InitStruct.Pull = GPIO_NOPULL;
  GPIO_InitStruct.Speed = GPIO_SPEED_FREQ_VERY_HIGH;
  GPIO_InitStruct.Alternate = GPIO_AF12_FMC;

  HAL_GPIO_Init(GPIOD, &GPIO_InitStruct);

  /* USER CODE BEGIN FMC_MspInit 1 */

  /* USER CODE END FMC_MspInit 1 */
}

void HAL_SRAM_MspInit(SRAM_HandleTypeDef* sramHandle){
  /* USER CODE BEGIN SRAM_MspInit 0 */

  /* USER CODE END SRAM_MspInit 0 */
  HAL_FMC_MspInit();
  /* USER CODE BEGIN SRAM_MspInit 1 */

  /* USER CODE END SRAM_MspInit 1 */
}

static uint32_t FMC_DeInitialized = 0;

static void HAL_FMC_MspDeInit(void){
  /* USER CODE BEGIN FMC_MspDeInit 0 */

  /* USER CODE END FMC_MspDeInit 0 */
  if (FMC_DeInitialized) {
    return;
  }
  FMC_DeInitialized = 1;
  /* Peripheral clock enable */
  __HAL_RCC_FMC_CLK_DISABLE();

  /** FMC GPIO Configuration
  PF0   ------> FMC_A0
  PE7   ------> FMC_D4
  PE8   ------> FMC_D5
  PE9   ------> FMC_D6
  PE10   ------> FMC_D7
  PE11   ------> FMC_D8
  PE12   ------> FMC_D9
  PE13   ------> FMC_D10
  PE14   ------> FMC_D11
  PE15   ------> FMC_D12
  PD8   ------> FMC_D13
  PD9   ------> FMC_D14
  PD10   ------> FMC_D15
  PD13   ------> FMC_A18
  PD14   ------> FMC_D0
  PD15   ------> FMC_D1
  PD0   ------> FMC_D2
  PD1   ------> FMC_D3
  PD4   ------> FMC_NOE
  PD5   ------> FMC_NWE
  PD7   ------> FMC_NE1
  */

  HAL_GPIO_DeInit(GPIOF, GPIO_PIN_0);

  HAL_GPIO_DeInit(GPIOE, GPIO_PIN_7|GPIO_PIN_8|GPIO_PIN_9|GPIO_PIN_10
                          |GPIO_PIN_11|GPIO_PIN_12|GPIO_PIN_13|GPIO_PIN_14
                          |GPIO_PIN_15);

  HAL_GPIO_DeInit(GPIOD, GPIO_PIN_8|GPIO_PIN_9|GPIO_PIN_10|GPIO_PIN_13
                          |GPIO_PIN_14|GPIO_PIN_15|GPIO_PIN_0|GPIO_PIN_1
                          |GPIO_PIN_4|GPIO_PIN_5|GPIO_PIN_7);

  /* USER CODE BEGIN FMC_MspDeInit 1 */

  /* USER CODE END FMC_MspDeInit 1 */
}

void HAL_SRAM_MspDeInit(SRAM_HandleTypeDef* sramHandle){
  /* USER CODE BEGIN SRAM_MspDeInit 0 */

  /* USER CODE END SRAM_MspDeInit 0 */
  HAL_FMC_MspDeInit();
  /* USER CODE BEGIN SRAM_MspDeInit 1 */

  /* USER CODE END SRAM_MspDeInit 1 */
}
/**
  * @}
  */

/**
  * @}
  */

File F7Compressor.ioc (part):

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Mcu.Name=STM32H723ZGTx
Mcu.Package=LQFP144
Mcu.UserName=STM32H723ZGTx
PA13(JTMS/SWDIO).GPIOParameters=GPIO_Label
PA13(JTMS/SWDIO).GPIO_Label=SWDIO
PA13(JTMS/SWDIO).Mode=Serial_Wire
PA13(JTMS/SWDIO).Signal=DEBUG_JTMS-SWDIO
PA14(JTCK/SWCLK).GPIOParameters=GPIO_Label
PA14(JTCK/SWCLK).GPIO_Label=SWCLK
PA14(JTCK/SWCLK).Mode=Serial_Wire
PA14(JTCK/SWCLK).Signal=DEBUG_JTCK-SWCLK
PA3.Signal=ADCx_INP15
PC0.GPIOParameters=GPIO_PuPd,GPIO_Label,GPIO_ModeDefaultEXTI
PC0.GPIO_Label=OIL_SW
PC0.GPIO_ModeDefaultEXTI=GPIO_MODE_IT_RISING_FALLING
PC0.GPIO_PuPd=GPIO_PULLUP
PC0.Signal=GPXTI0
PC14-OSC32_IN.Signal=RCC_OSC32_IN
PC15-OSC32_OUT.Signal=RCC_OSC32_OUT
PC2_C.GPIOParameters=GPIO_PuPd,GPIO_Label,GPIO_ModeDefaultEXTI
PC2_C.GPIO_Label=ESTOP
PC2_C.GPIO_ModeDefaultEXTI=GPIO_MODE_IT_FALLING
PC2_C.GPIO_PuPd=GPIO_PULLUP
PC2_C.Signal=GPXTI2
PC6.Signal=S_TIM3_CH1
PD0.Signal=FMC_D2_DA2
PD1.Signal=FMC_D3_DA3
PD10.Signal=FMC_D15_DA15
PD13.Signal=FMC_A18
PD14.Signal=FMC_D0_DA0
PD15.Signal=FMC_D1_DA1
PD4.Signal=FMC_NOE
PD5.Signal=FMC_NWE
PD7.Mode=NorPsramChipSelect1_1
PD7.Signal=FMC_NE1
PD8.Signal=FMC_D13_DA13
PD9.Signal=FMC_D14_DA14
PE10.Signal=FMC_D7_DA7
PE11.Signal=FMC_D8_DA8
PE12.Signal=FMC_D9_DA9
PE13.Signal=FMC_D10_DA10
PE14.Signal=FMC_D11_DA11
PE15.Signal=FMC_D12_DA12
PE7.Signal=FMC_D4_DA4
PE8.Signal=FMC_D5_DA5
PE9.Signal=FMC_D6_DA6
PF0.Signal=FMC_A0
PF10.GPIOParameters=PinState,GPIO_Label
PF10.GPIO_Label=TP_CS
PF10.PinState=GPIO_PIN_SET
PF10.Signal=GPIO_Output
PF7.Mode=Full_Duplex_Master
PF7.Signal=SPI5_SCK
PF8.Mode=Full_Duplex_Master
PF8.Signal=SPI5_MISO
PF9.Mode=Full_Duplex_Master
PF9.Signal=SPI5_MOSI
PG2.GPIOParameters=PinState,GPIO_Label
PG2.GPIO_Label=LCD_RST
PG2.PinState=GPIO_PIN_SET
PG2.Signal=GPIO_Output
PG3.GPIOParameters=GPIO_PuPd,GPIO_Label,GPIO_ModeDefaultEXTI
PG3.GPIO_Label=TP_IRQ
PG3.GPIO_ModeDefaultEXTI=GPIO_MODE_IT_FALLING
PG3.GPIO_PuPd=GPIO_PULLUP
PG3.Signal=GPXTI3
PG4.GPIOParameters=GPIO_Label
PG4.GPIO_Label=RELAY_START
PG4.Signal=GPIO_Output
PG5.GPIOParameters=GPIO_Label
PG5.GPIO_Label=RELAY_STOP
PG5.Signal=GPIO_Output
PH0-OSC_IN.Mode=HSE-External-Oscillator
PH0-OSC_IN.Signal=RCC_OSC_IN
PH1-OSC_OUT.Mode=HSE-External-Oscillator
PH1-OSC_OUT.Signal=RCC_OSC_OUT
RCC.HSE_VALUE=8000000
RCC.SYSCLKFreq_VALUE=480000000
RCC.SYSCLKSource=RCC_SYSCLKSOURCE_PLLCLK
board=NUCLEO-H723ZG
boardIOC=true

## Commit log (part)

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2026-05-10 Iniital Commit
2026-05-13 UI and State machine code 1st pass
2026-05-15 changes to UI and hihi shutdown
2026-05-22 Change from 2 relays to one relay
2026-05-22 comments updated
2026-05-31 fixed to toolchain
2026-05-31 fixes to toolpaths
2026-06-06 converted to Jlink debugger
2026-06-06 Changes to Makefile to fix JLink errors (make flash)
2026-06-07 updated pin numbers on wiring_diagram.html
2026-06-10 added claude_resume.txt
2026-06-13 Added abilty to use Segger Ozone as a debugger
2026-06-13 Fiixed now where Ozone auto loads jdebug correctly
2026-06-13 gitignore changes
2026-06-13 still issues with gitignore
2026-06-13 still gitignore
2026-06-13 added make cppcheck
2026-06-13 git ignore
2026-06-13 gitignore
